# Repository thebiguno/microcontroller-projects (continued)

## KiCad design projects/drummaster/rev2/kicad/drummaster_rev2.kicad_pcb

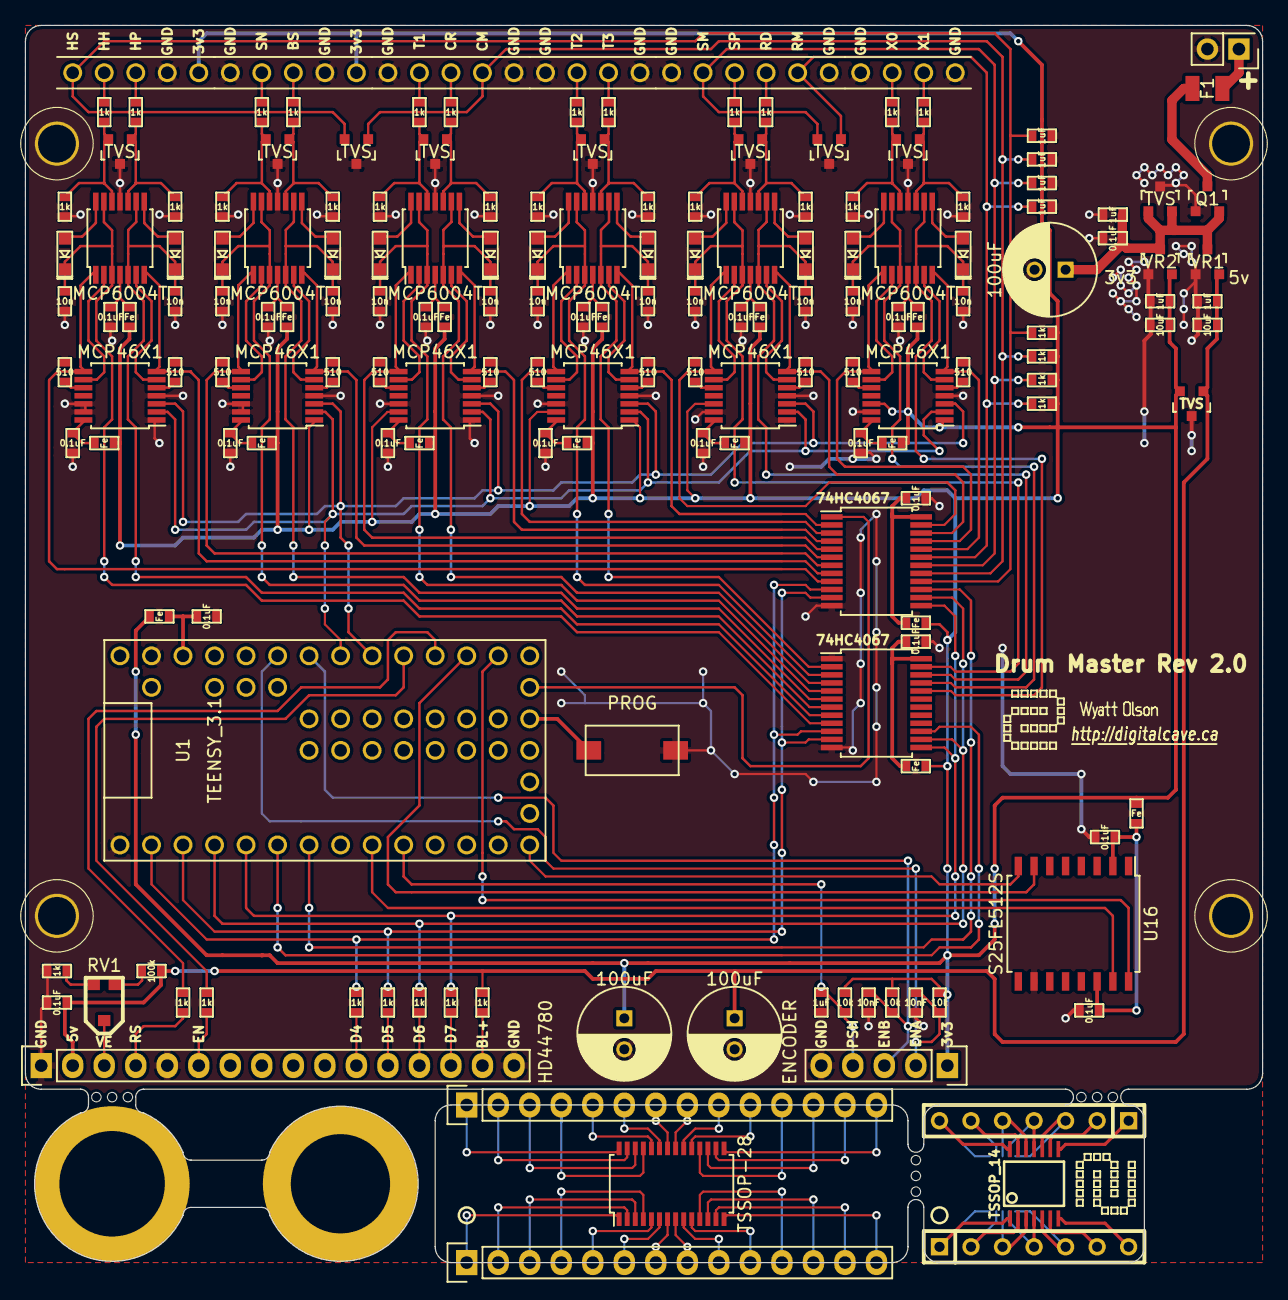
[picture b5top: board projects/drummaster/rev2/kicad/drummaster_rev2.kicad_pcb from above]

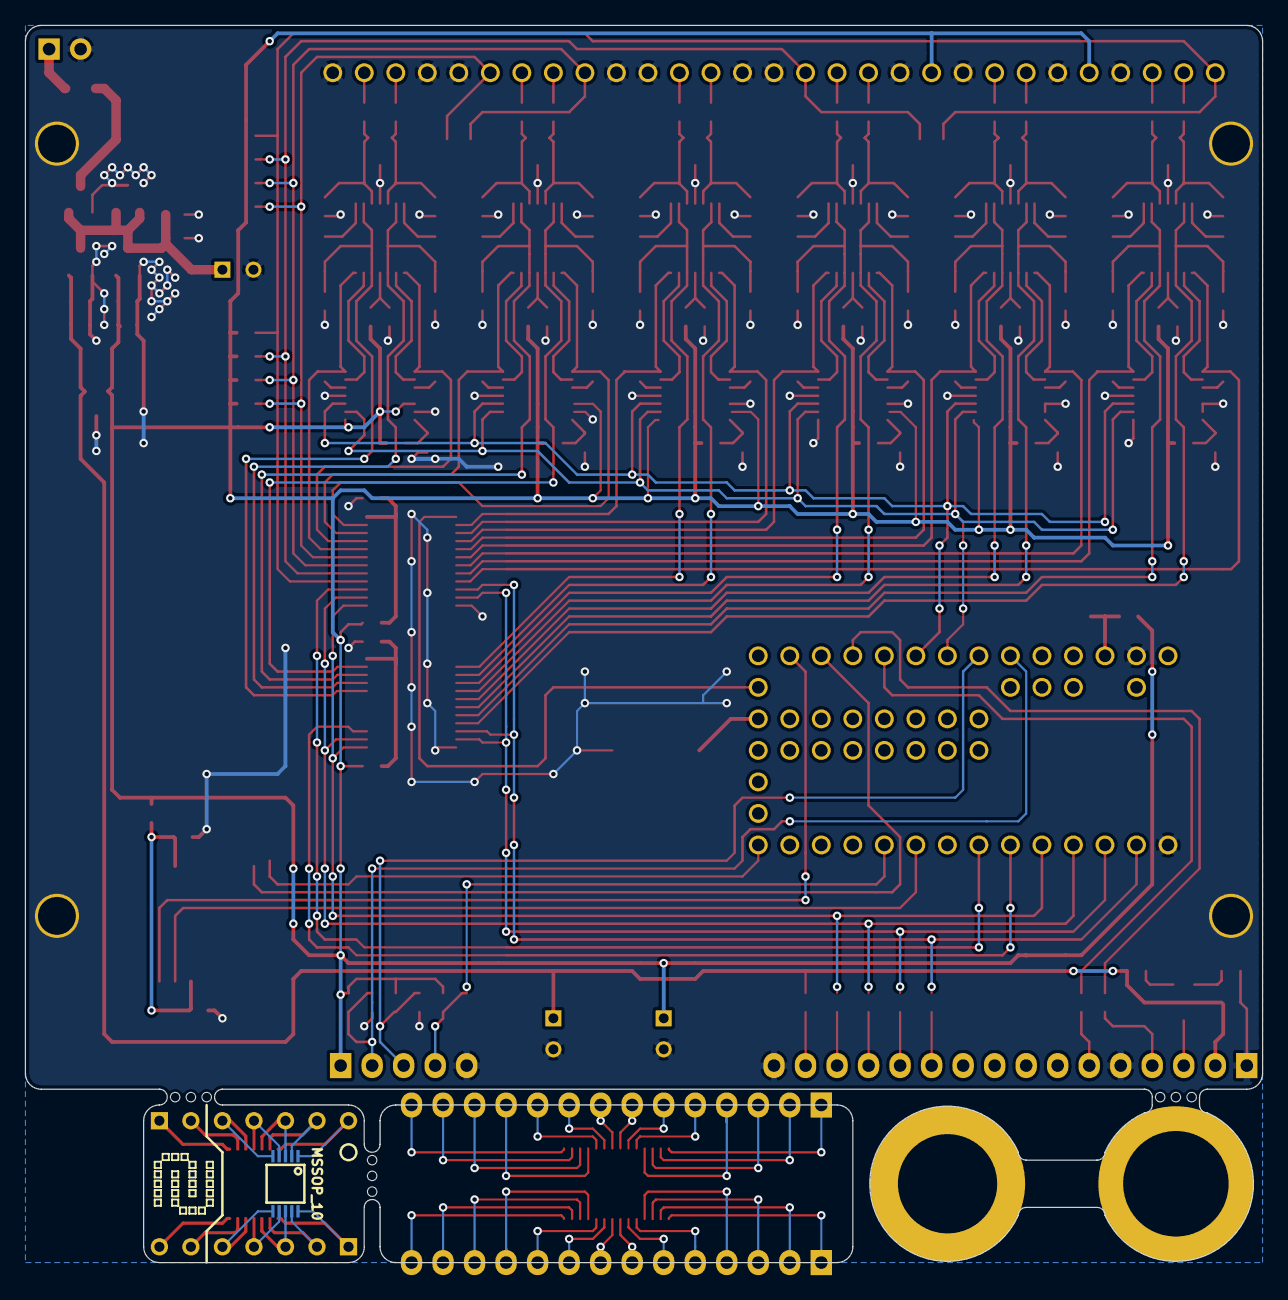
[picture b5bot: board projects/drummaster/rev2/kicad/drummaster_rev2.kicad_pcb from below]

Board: 2 copper layers, 99.7 x 99.7 mm, 186 parts (2 on the bottom side), 181 nets.

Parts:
C1, C2, C3, C4, C5, C6, C19, C20, C21, C22, C23, C25, C27, C31, C32, C33, C36, C37, C38: 0.1uF; SM0603_VALUE
C7, C8, C9, C10, C11, C12, C13, C14, C15, C16, C17, C18: 10n; SM0603_VALUE
C24, C30, C39: 100uF; C_Radial_D7.5_L11.2_P2.5
C26, C29, C35, C42, C43, C44, C45, C46: 1uF; SM0603_VALUE
C28, C34: 10uF; SM0603_VALUE
C40, C41: 10nF; SM0603_VALUE
D1, D2, D3, D4, D5, D6, D7, D8, D21, D22: TVS; SOT-23
D9, D10, D11, D12, D13, D14, D15, D16, D17, D18, D19, D20: DIODESCH; SOD-323_DIODE
DS1: HD44780; Pin_Header_Straight_1x16
F1: FUSE; Fuse_SMD1206_Reflow
K1, K2, K3: PINS_5; Pin_Header_Straight_1x05
K4, K6: PINS_4; Pin_Header_Straight_1x04
K5: PINS_6; Pin_Header_Straight_1x06
K7: ENCODER; Pin_Header_Straight_1x05
K101: TSSOP-28; TSSOP-28_4.4x9.7mm_Pitch0.65mm
K102, K103: DIP; Pin_Header_Straight_1x14
K201, K202: PINS_7; SIL-7
K203: MSSOP_10; MSOP10-0.5
K204: TSSOP_14; TSSOP14
L1, L2, L3, L4, L5, L6, L7, L8, L9, L10, L11, L12, L13, L14, L15, L16: Fe; SM0603_VALUE
MP1, MP2, MP3, MP4: MOUNTING_HOLE; MOUNTING_HOLE_#4
MP5: GRAPHIC; DIGITALCAVE_AUTHOR
MP6: GRAPHIC; DIGITALCAVE_LOGO
MP7: GRAPHIC; DIGITALCAVE_URL
P1: CONN_2; Pin_Header_Straight_2x01
Q1: MOSFET_P; SOT-23
R1, R2, R3, R4, R5, R6, R7, R8, R9, R10, R11, R12, R13, R14, R15, R16, R18, R19, R20, R21, R25, R26, R27, R28, R29, R30, R31, R32, R33, R34, R35, R36, R49, R50, R51, R52: 1k; SM0603_VALUE
R17: 100k; SM0603_VALUE
R22, R23, R24: 10k; SM0603_VALUE
R37, R38, R39, R40, R41, R42, R43, R44, R45, R46, R47, R48: 510; SM0603_VALUE
RV1: POTENTIOMETER; POTENTIOMETER_SMD
SW1: PROG; SW_6x3
U1: TEENSY_3.1
U2, U3, U4, U5, U6, U7: MCP6004T; TSSOP-14_4.4x5mm_Pitch0.65mm
U8, U9: 74HC4067; SSOP-24_5.3x8.2mm_Pitch0.65mm
U10, U11, U12, U13, U14, U15: MCP46X1; TSSOP-14_4.4x5mm_Pitch0.65mm
U16: S25FL512S; SOIC-16_7.5x10.3mm_Pitch1.27mm
VAL: REF; DIGITALCAVE_LOGO
VAL#2: REF; DIGITALCAVE_LOGO
VR1, VR2: MCP1702; SOT-23
mouse_bites: VAL**; mouse_bites
mouse_bites#2, mouse_bites#3: VAL**; mouse_bites

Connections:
+3V3: C34.1, C35.1, C39.1, D22.2, K1.1, K2.1, K7.1, L1.1, L2.1, L3.1, L4.1, L5.1, L6.1, L7.1, L8.1, L9.1, L10.1, L11.1, L12.1, L13.1, L14.1, L15.1, L16.2, R1.2, R2.2, R15.2, R16.2, R22.2, R23.2, R24.2, U11.1, U12.13, U13.1, U13.13, U14.12, U15.1, U15.12, VR2.2
+5V: C24.1, C25.1, C28.1, C29.1, D22.1, DS1.2, R17.1, R19.1, VR1.2
+9V: F1.1, P1.1
/ADC_ENABLE: U1.5, U9.15
/ADC_INPUT: U1.A14, U9.1
/BS: K2.3, R27.1
/BS_A: U3.7, U9.6, U11.7
/BS_D: C9.1, D11.2, U3.5, U3.9, U8.6
/CM: C44.2, D7.1, K3.2, R2.1, U9.17
/CR: K3.3, R29.1
/CR_A: U4.7, U9.4, U12.7
/CR_D: C11.1, D13.2, U4.5, U4.9, U8.4
/DISP_EN: R21.1, U1.17
/DISP_RS: R20.1, U1.16
/DRAIN_ENABLE: U1.4, U8.15
/ENC_A: C40.2, K7.2, R22.1, U1.21
/ENC_B: C41.2, K7.3, R23.1, U1.20
/ENC_PUSH: C42.2, K7.4, R24.1, U1.8
/HH: K1.4, R26.1
/HH_A: U2.1, U9.9, U10.8
/HH_D: C8.1, D10.2, U2.3, U2.13, U8.9
/HP: K1.3, R25.1
/HP_A: U2.7, U9.8, U10.7
/HP_D: C7.1, D9.2, U2.5, U2.9, U8.8
/HS: C43.2, D7.2, K1.5, R1.1, U9.16
/MEM2CS: U1.15, U16.7
/MISO: U1.12, U16.8
/MOSI: U1.7, U16.15
/MUX0: R49.1, U1.0, U8.10, U9.10
/MUX1: R50.1, U1.1, U8.11, U9.11
/MUX2: R51.1, U1.2, U8.14, U9.14
/MUX3: R52.1, U1.3, U8.13, U9.13
/RD: K5.3, R33.1
/RD_A: U6.7, U9.22, U14.7
/RD_D: C15.1, D17.2, U6.5, U6.9, U8.22
/RM: C46.2, D8.1, K5.2, R16.1, U9.19
/SCL: U1.19, U10.2, U11.2, U12.2, U13.2, U14.2, U15.2
/SCLK: U1.14, U16.16
/SDA: U1.18, U10.3, U11.3, U12.3, U13.3, U14.3, U15.3
/SM: C45.2, D8.2, K5.5, R15.1, U9.18
/SN: K2.4, R28.1
/SN_A: U3.1, U9.7, U11.8
/SN_D: C10.1, D12.2, U3.3, U3.13, U8.7
/SP: K5.4, R34.1
/SP_A: U6.1, U9.23, U14.8
/SP_D: C16.1, D18.2, U6.3, U6.13, U8.23
/T1: K3.4, R30.1
/T1_A: U4.1, U9.5, U12.8
/T1_D: C12.1, D14.2, U4.3, U4.13, U8.5
/T2: K4.3, R32.1
/T2_A: U5.1, U9.3, U13.8
/T2_D: C14.1, D16.2, U5.3, U5.13, U8.3
/T3: K4.2, R31.1
/T3_A: U5.7, U9.2, U13.7
/T3_D: C13.1, D15.2, U5.5, U5.9, U8.2
/X0: K6.3, R36.1
/X0_A: U7.1, U9.21, U15.8
/X0_D: C18.1, D20.2, U7.3, U7.13, U8.21
/X1: K6.2, R35.1
/X1_A: U7.7, U9.20, U15.7
/X1_D: C17.1, D19.2, U7.5, U7.9, U8.20
GND: C1.2, C2.2, C3.2, C4.2, C5.2, C6.2, C7.2, C8.2, C9.2, C10.2, C11.2, C12.2, C13.2, C14.2, C15.2, C16.2, C17.2, C18.2, C19.2, C20.2, C21.2, C22.2, C23.2, C24.2, C25.2, C26.1, C27.1, C28.2, C29.2, C30.2, C31.2, C32.2, C33.2, C34.2, C35.2, C36.2, C37.2, C38.2, C39.2, C40.1, C41.1, C42.1, C43.1, C44.1, C45.1, C46.1, D1.3, D2.3, D3.3, D4.3, D5.3, D6.3, D7.3, D8.3, D21.3, D22.3, DS1.1, DS1.5, DS1.16, K1.2, K2.2, K2.5, K3.1, K3.5, K4.1, K4.4, K5.1, K5.6, K6.1, K6.4, K7.5, MP1.1, MP2.1, MP3.1, MP4.1, P1.2, Q1.G, R3.2, R4.2, R5.2, R6.2, R7.2, R8.2, R9.2, R10.2, R11.2, R12.2, R13.2, R14.2, R18.2, R37.1, R38.1, R39.1, R40.1, R41.1, R42.1, R43.1, R44.1, R45.1, R46.1, R47.1, R48.1, SW1.1, U1.AGND, U1.GND, U2.11, U3.11, U4.11, U5.11, U6.11, U7.11, U8.1, U8.12, U9.12, U10.1, U10.4, U10.12, U10.13, U11.4, U11.12, U11.13, U12.1, U12.4, U12.12, U13.4, U13.12, U14.1, U14.4, U14.13, U15.4, U15.13, U16.10, VR1.1, VR2.1
unnamed: K202.2, K204.9
unnamed: K202.1, K204.8
unnamed: K201.7, K204.7
unnamed: K201.6, K204.6
unnamed: K202.3, K203.5, K204.10
unnamed: K201.5, K203.6, K204.5
unnamed: K201.4, K203.7, K204.4
unnamed: K202.4, K203.4, K204.11
unnamed: K202.5, K203.3, K204.12
unnamed: K202.6, K203.2, K204.13
unnamed: K202.7, K203.1, K204.14
unnamed: K201.3, K203.8, K204.3
unnamed: K201.2, K203.9, K204.2
unnamed: K201.1, K203.10, K204.1
unnamed: C1.1, L1.2, U2.4
unnamed: C2.1, L2.2, U3.4
unnamed: C3.1, L3.2, U4.4
unnamed: C4.1, L4.2, U5.4
unnamed: C5.1, L5.2, U6.4
unnamed: C6.1, L6.2, U7.4
unnamed: C19.1, L7.2, U8.24
unnamed: C20.1, L8.2, U10.14
unnamed: C21.1, L9.2, U11.14
unnamed: C22.1, L10.2, U12.14
unnamed: C23.1, L11.2, U9.24
unnamed: C26.2, C27.2, C30.1, D21.1, D21.2, Q1.S, VR1.3, VR2.3
unnamed: C31.1, L12.2, U13.14
unnamed: C32.1, L13.2, U14.14
unnamed: C33.1, L14.2, U15.14
unnamed: C36.1, C37.1, L15.2, U16.2, U16.14
unnamed: C38.1, L16.1, U1.3v3
unnamed: D1.1, R7.1, R25.2, U2.10
unnamed: D1.2, R8.1, R26.2, U2.12
unnamed: D2.1, R9.1, R27.2, U3.10
unnamed: D2.2, R10.1, R28.2, U3.12
unnamed: D3.1, R11.1, R29.2, U4.10
unnamed: D3.2, R12.1, R30.2, U4.12
unnamed: D4.1, R13.1, R31.2, U5.10
unnamed: D4.2, R14.1, R32.2, U5.12
unnamed: D5.1, R3.1, R33.2, U6.10
unnamed: D5.2, R4.1, R34.2, U6.12
unnamed: D6.1, R5.1, R35.2, U7.10
unnamed: D6.2, R6.1, R36.2, U7.12
unnamed: D9.1, U2.8
unnamed: D10.1, U2.14
unnamed: D11.1, U3.8
unnamed: D12.1, U3.14
unnamed: D13.1, U4.8
unnamed: D14.1, U4.14
unnamed: D15.1, U5.8
unnamed: D16.1, U5.14
unnamed: D17.1, U6.8
unnamed: D18.1, U6.14
unnamed: D19.1, U7.8
unnamed: D20.1, U7.14
unnamed: DS1.3, RV1.3
unnamed: DS1.4, R20.2
unnamed: DS1.6, R21.2
unnamed: DS1.11, R49.2
unnamed: DS1.12, R50.2
unnamed: DS1.13, R51.2
unnamed: DS1.14, R52.2
unnamed: DS1.15, R19.2
unnamed: F1.2, Q1.D
unnamed: K101.1, K102.1
unnamed: K101.2, K102.2
unnamed: K101.3, K102.3
unnamed: K101.4, K102.4
unnamed: K101.5, K102.5
unnamed: K101.6, K102.6
unnamed: K101.7, K102.7
unnamed: K101.8, K102.8
unnamed: K101.9, K102.9
unnamed: K101.10, K102.10
unnamed: K101.11, K102.11
unnamed: K101.12, K102.12
unnamed: K101.13, K102.13
unnamed: K101.14, K102.14
unnamed: K101.15, K103.14
unnamed: K101.16, K103.13
unnamed: K101.17, K103.12
unnamed: K101.18, K103.11
unnamed: K101.19, K103.10
unnamed: K101.20, K103.9
unnamed: K101.21, K103.8
unnamed: K101.22, K103.7
unnamed: K101.23, K103.6
unnamed: K101.24, K103.5
unnamed: K101.25, K103.4
unnamed: K101.26, K103.3
unnamed: K101.27, K103.2
unnamed: K101.28, K103.1
unnamed: R17.2, RV1.2
unnamed: R18.1, RV1.1
unnamed: R37.2, U10.10
unnamed: R38.2, U10.5
unnamed: R39.2, U11.10
unnamed: R40.2, U11.5
unnamed: R41.2, U12.10
unnamed: R42.2, U12.5
unnamed: R43.2, U13.10
unnamed: R44.2, U13.5
unnamed: R45.2, U14.10
unnamed: R46.2, U14.5
unnamed: R47.2, U15.10
unnamed: R48.2, U15.5
unnamed: SW1.2, U1.PRG
unnamed: U2.6, U10.6
unnamed: U2.2, U10.9
unnamed: U3.6, U11.6
unnamed: U3.2, U11.9
unnamed: U4.6, U12.6
unnamed: U4.2, U12.9
unnamed: U5.6, U13.6
unnamed: U5.2, U13.9
unnamed: U6.6, U14.6
unnamed: U6.2, U14.9
unnamed: U7.6, U15.6
unnamed: U7.2, U15.9

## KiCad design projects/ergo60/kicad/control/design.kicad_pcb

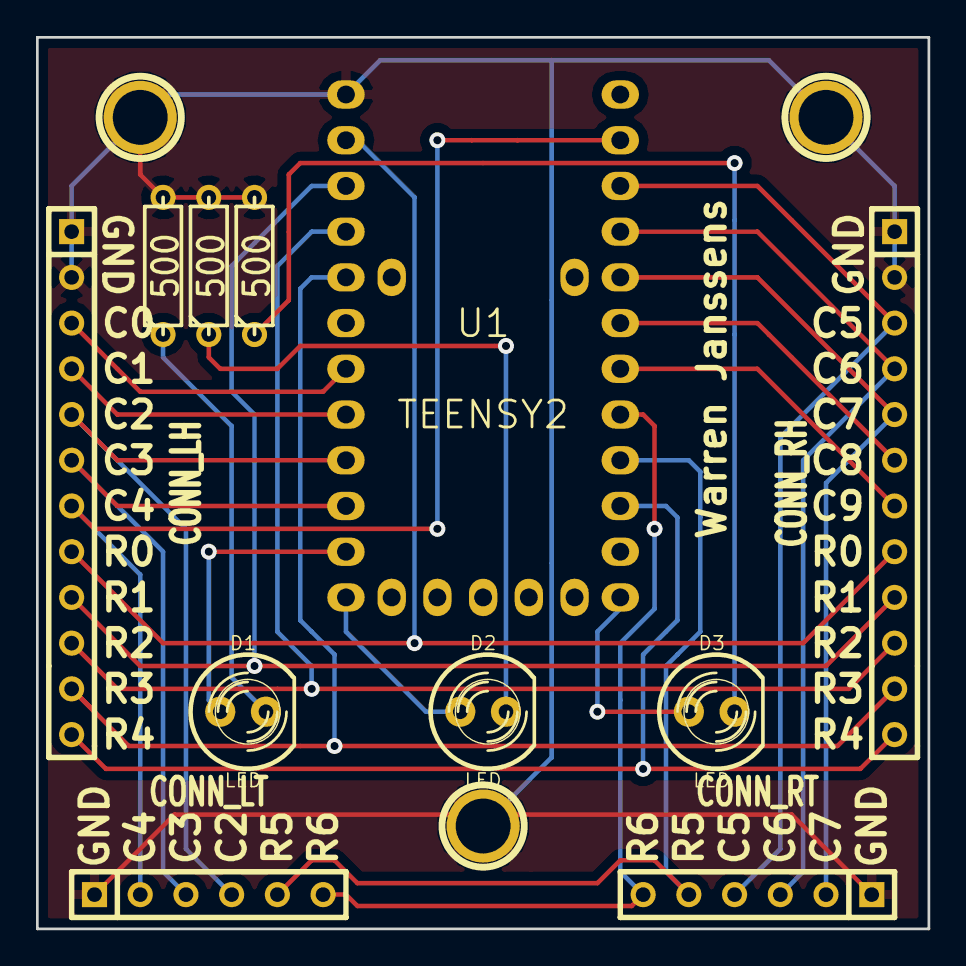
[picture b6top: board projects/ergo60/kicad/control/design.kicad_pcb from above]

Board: 2 copper layers, 49.5 x 49.5 mm, 14 parts (0 on the bottom side), 24 nets.

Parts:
D1, D2, D3: LED; LED-5MM
P1: CONN_LH; SIL-12
P2: CONN_RH; SIL-12
P3: CONN_LT; SIL-6
P4: CONN_RT; SIL-6
P5, P6, P7: CONN_1; 1pin
R1, R2, R3: 500; R3
U1: TEENSY2; Teensy2

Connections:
C0: P1.3, U1.7
C1: P1.4, U1.8
C2: P1.5, P3.4, U1.9
C3: P1.6, P3.3, U1.10
C4: P1.7, P3.2, U1.23
C5: P2.3, P4.4, U1.22
C6: P2.4, P4.3, U1.21
C7: P2.5, P4.2, U1.20
C8: P2.6, U1.19
C9: P2.7, U1.18
GND: P1.1, P1.2, P2.1, P2.2, P3.1, P4.1, P5.1, P6.1, P7.1, R1.2, R2.2, R3.2, U1.1
L0: D1.1, U1.11
L1: D2.1, U1.12
L2: D3.1, U1.13
unnamed: D1.2, R1.1
unnamed: D2.2, R2.1
unnamed: D3.2, R3.1
R0: P1.8, P2.8, U1.2
R1: P1.9, P2.9, U1.3
R2: P1.10, P2.10, U1.4
R3: P1.11, P2.11, U1.5
R4: P1.12, P2.12, U1.15
R5: P3.5, P4.5, U1.16
R6: P3.6, P4.6, U1.17

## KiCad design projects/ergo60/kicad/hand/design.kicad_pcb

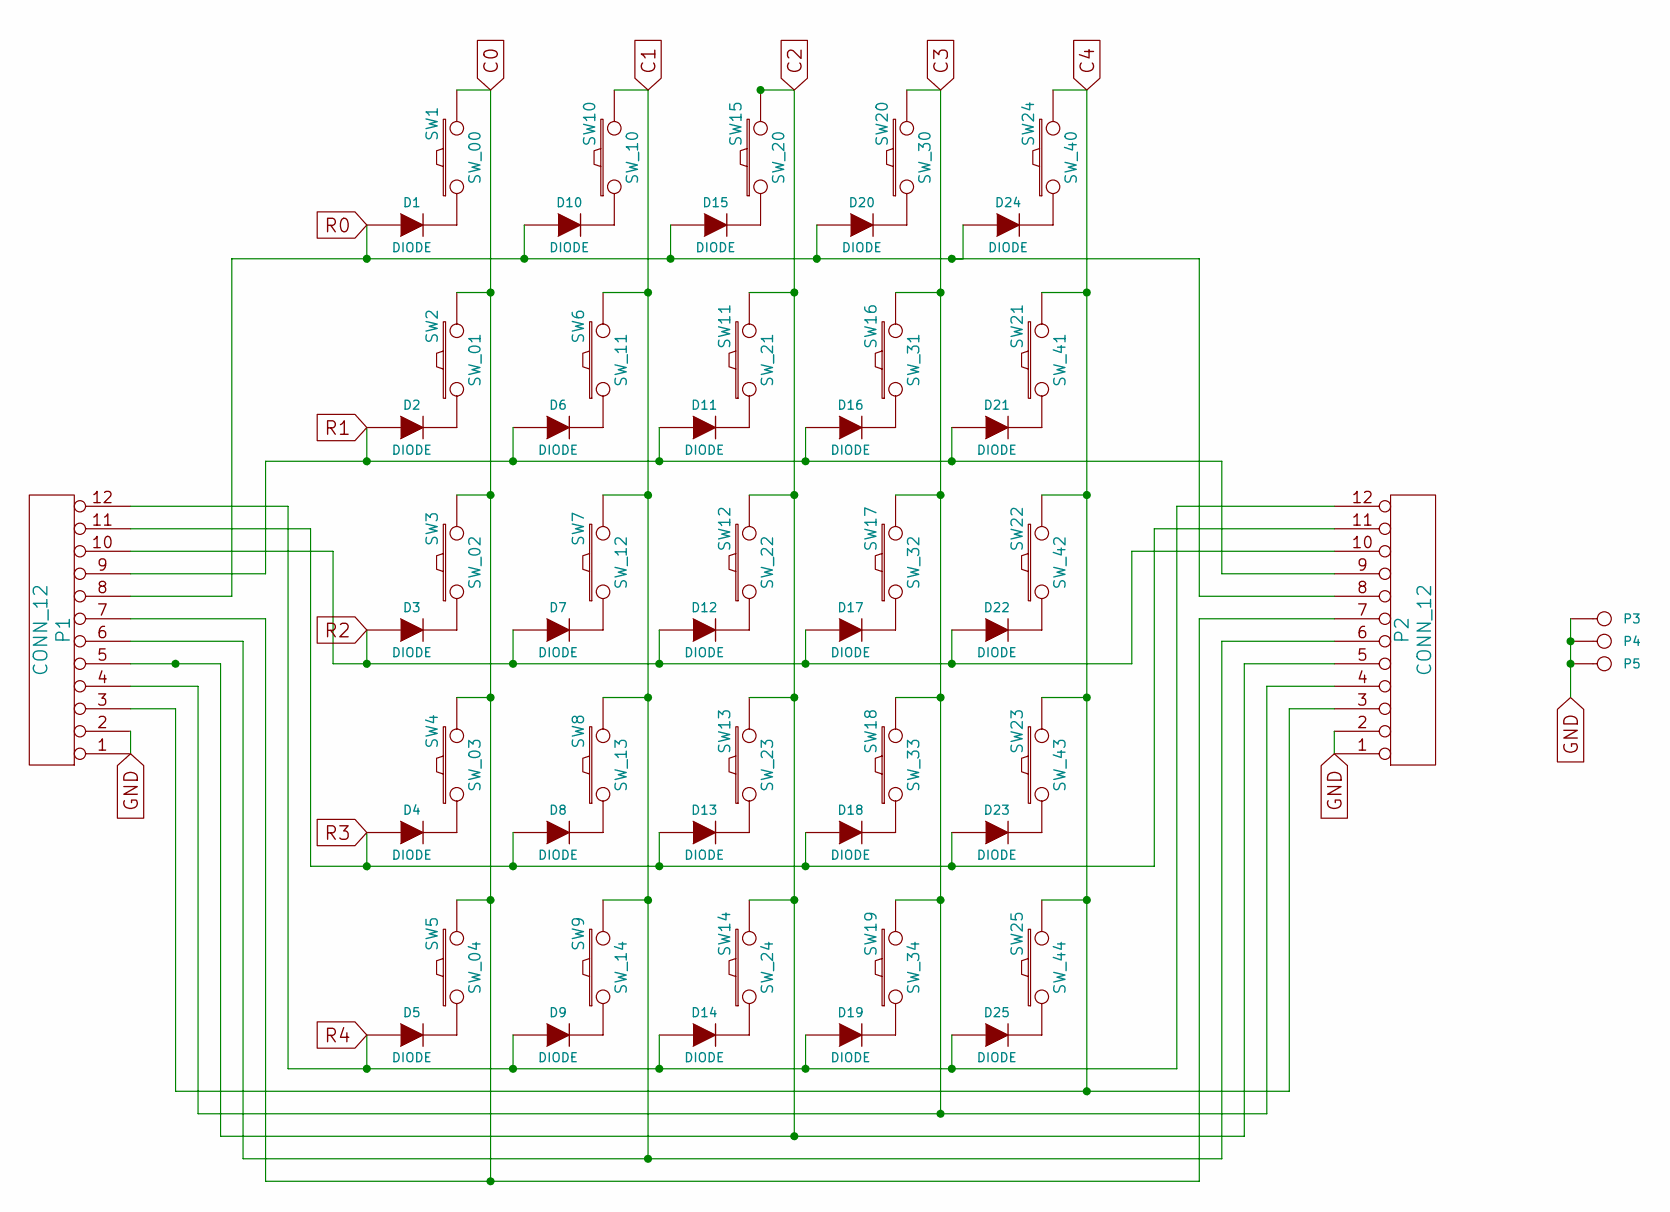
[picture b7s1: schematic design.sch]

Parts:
D1, D2, D3, D4, D5, D6, D7, D8, D9, D10, D11, D12, D13, D14, D15, D16, D17, D18, D19, D20, D21, D22, D23, D24, D25: DIODE
P1, P2: CONN_12
P3, P4, P5: CONN_1
SW1: SW_00
SW2: SW_01
SW3: SW_02
SW4: SW_03
SW5: SW_04
SW6: SW_11
SW7: SW_12
SW8: SW_13
SW9: SW_14
SW10: SW_10
SW11: SW_21
SW12: SW_22
SW13: SW_23
SW14: SW_24
SW15: SW_20
SW16: SW_31
SW17: SW_32
SW18: SW_33
SW19: SW_34
SW20: SW_30
SW21: SW_41
SW22: SW_42
SW23: SW_43
SW24: SW_40
SW25: SW_44

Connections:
C0: P1.7, P2.7, SW1.2, SW2.2, SW3.2, SW4.2, SW5.2
C1: P1.6, P2.6, SW6.2, SW7.2, SW8.2, SW9.2, SW10.2
C2: P1.5, P2.5, SW11.2, SW12.2, SW13.2, SW14.2, SW15.2
C3: P1.4, P2.4, SW16.2, SW17.2, SW18.2, SW19.2, SW20.2
C4: P1.3, P2.3, SW21.2, SW22.2, SW23.2, SW24.2, SW25.2
GND: P1.1, P1.2, P2.1, P2.2, P3.1, P4.1, P5.1
unnamed: D17.2 (K), SW17.1
unnamed: D12.2 (K), SW12.1
unnamed: D7.2 (K), SW7.1
unnamed: D3.2 (K), SW3.1
unnamed: D21.2 (K), SW21.1
unnamed: D18.2 (K), SW18.1
unnamed: D13.2 (K), SW13.1
unnamed: D8.2 (K), SW8.1
unnamed: D4.2 (K), SW4.1
unnamed: D22.2 (K), SW22.1
unnamed: D20.2 (K), SW20.1
unnamed: D15.2 (K), SW15.1
unnamed: D24.2 (K), SW24.1
unnamed: D10.2 (K), SW10.1
unnamed: D1.2 (K), SW1.1
unnamed: D16.2 (K), SW16.1
unnamed: D11.2 (K), SW11.1
unnamed: D6.2 (K), SW6.1
unnamed: D2.2 (K), SW2.1
unnamed: D14.2 (K), SW14.1
unnamed: D9.2 (K), SW9.1
unnamed: D5.2 (K), SW5.1
unnamed: D23.2 (K), SW23.1
unnamed: D25.2 (K), SW25.1
unnamed: D19.2 (K), SW19.1
R0: D1.1 (A), D10.1 (A), D15.1 (A), D20.1 (A), D24.1 (A), P1.8, P2.8
R1: D2.1 (A), D6.1 (A), D11.1 (A), D16.1 (A), D21.1 (A), P1.9, P2.9
R2: D3.1 (A), D7.1 (A), D12.1 (A), D17.1 (A), D22.1 (A), P1.10, P2.10
R3: D4.1 (A), D8.1 (A), D13.1 (A), D18.1 (A), D23.1 (A), P1.11, P2.11
R4: D5.1 (A), D9.1 (A), D14.1 (A), D19.1 (A), D25.1 (A), P1.12, P2.12

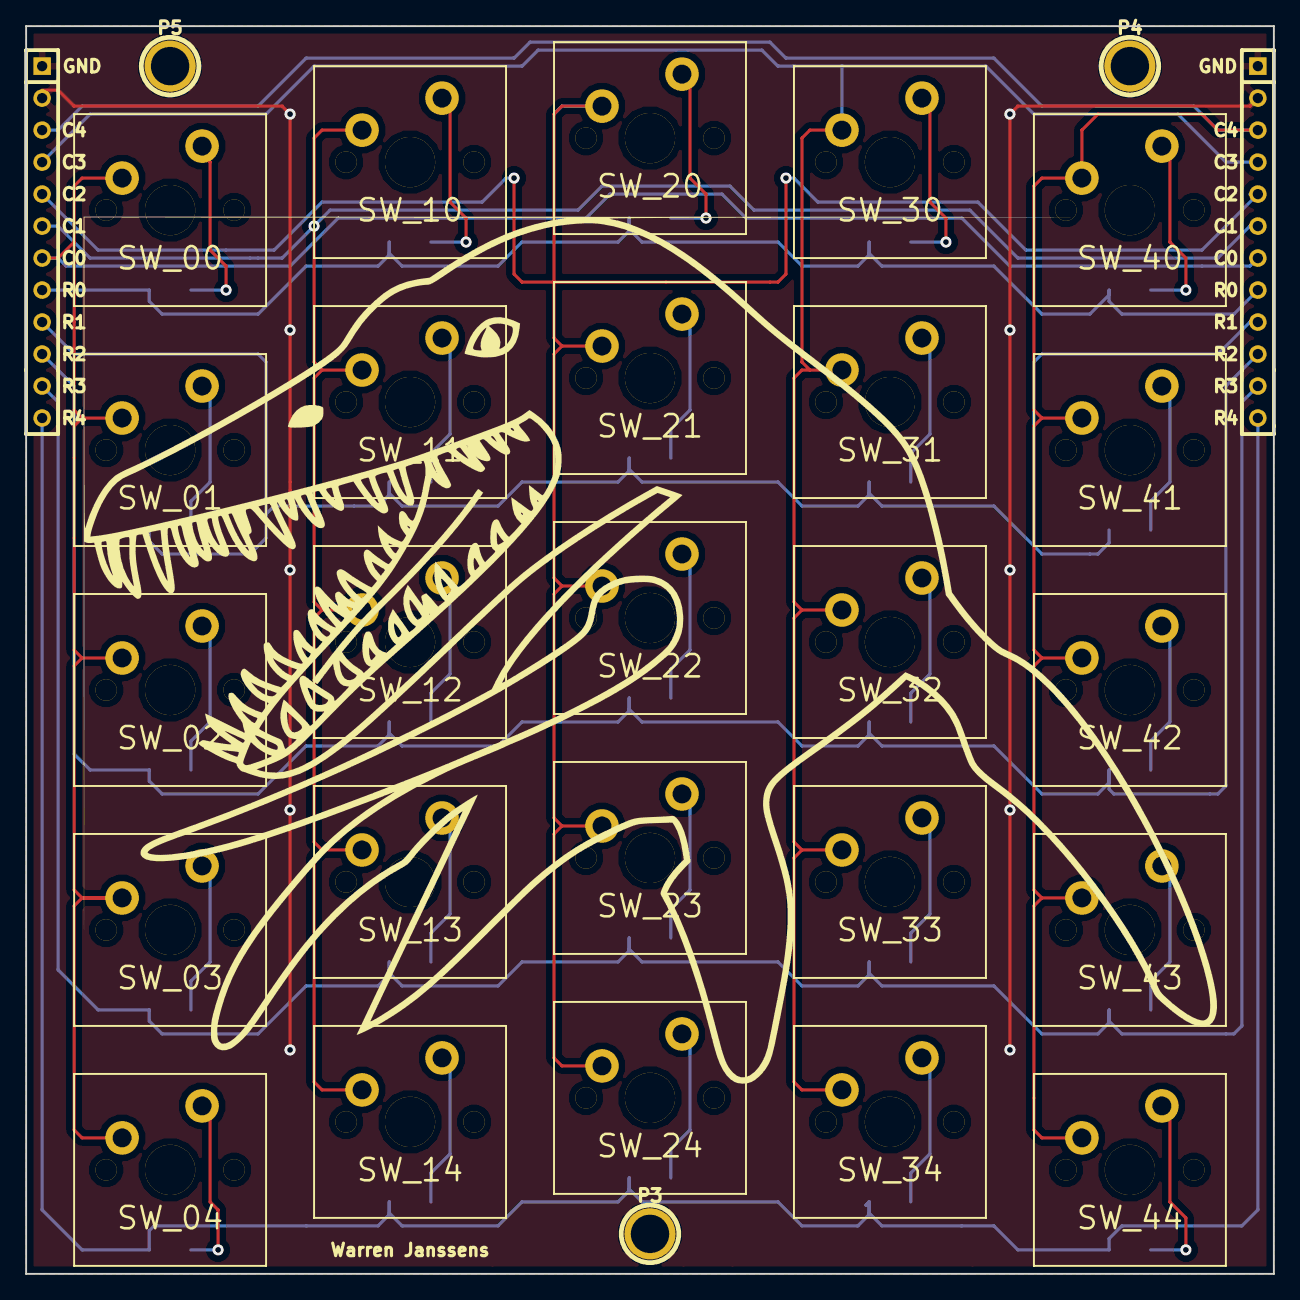
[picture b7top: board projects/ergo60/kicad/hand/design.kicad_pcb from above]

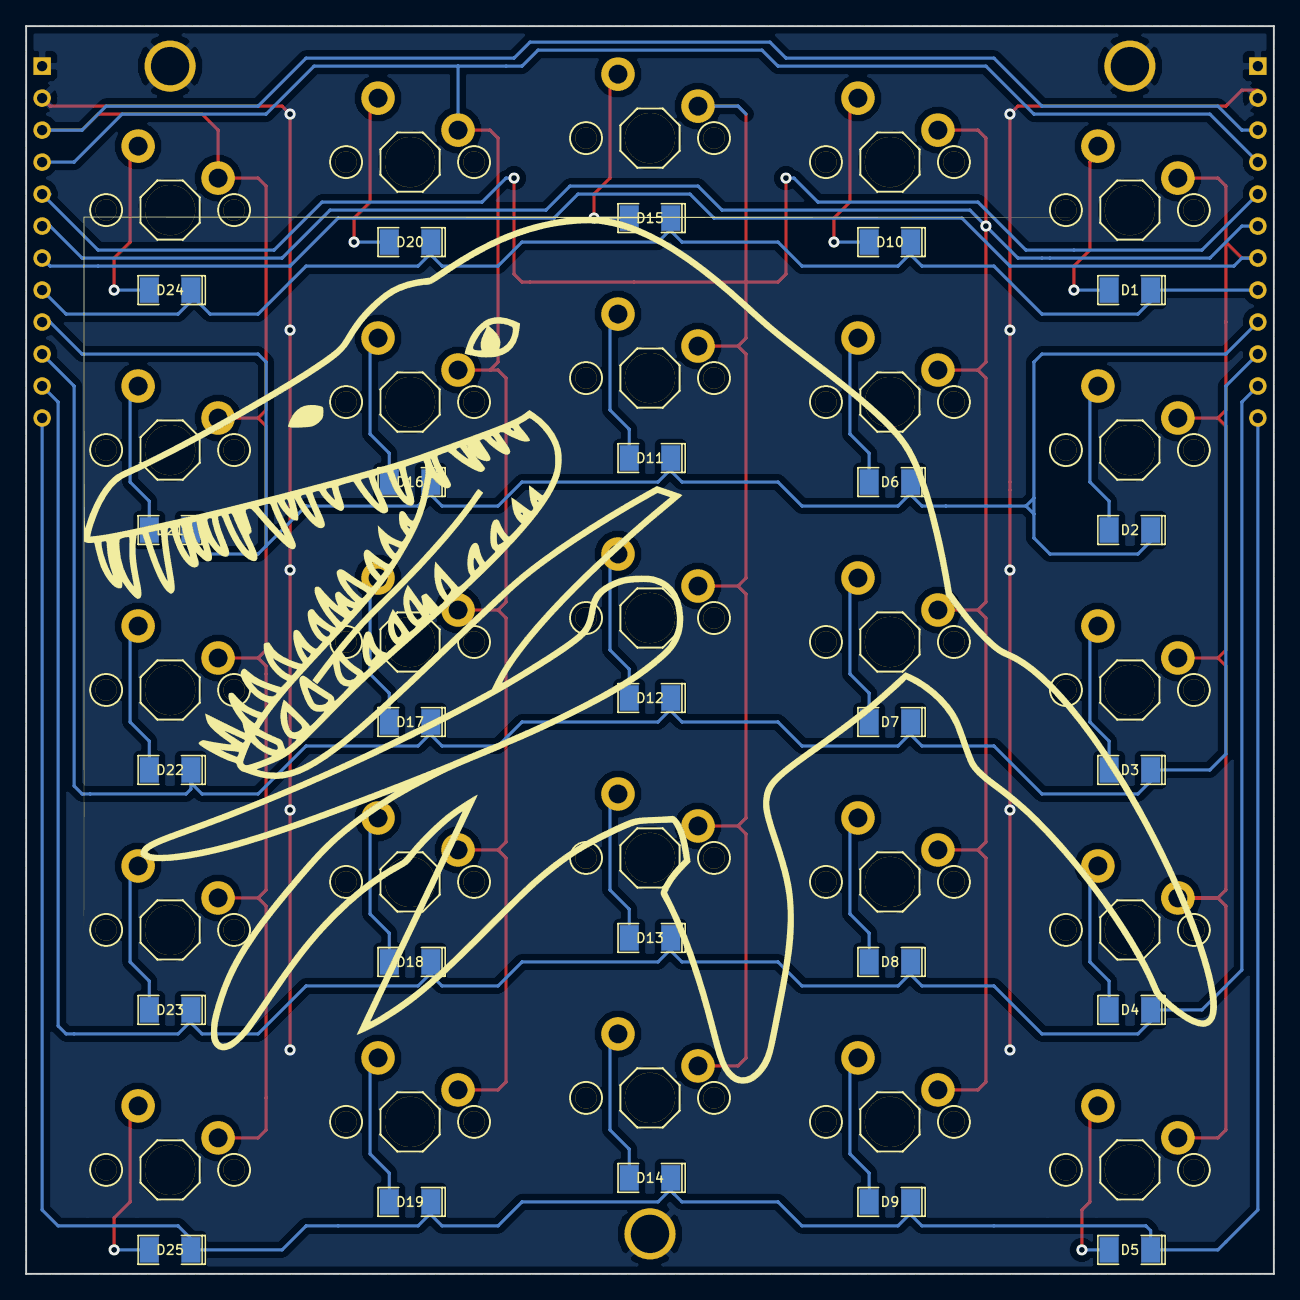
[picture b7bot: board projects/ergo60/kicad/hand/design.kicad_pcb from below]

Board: 2 copper layers, 99.1 x 99.1 mm, 57 parts (25 on the bottom side), 36 nets.

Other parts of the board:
VAL: plesiosaurus_back
VAL#2: plesiosaurus_front
